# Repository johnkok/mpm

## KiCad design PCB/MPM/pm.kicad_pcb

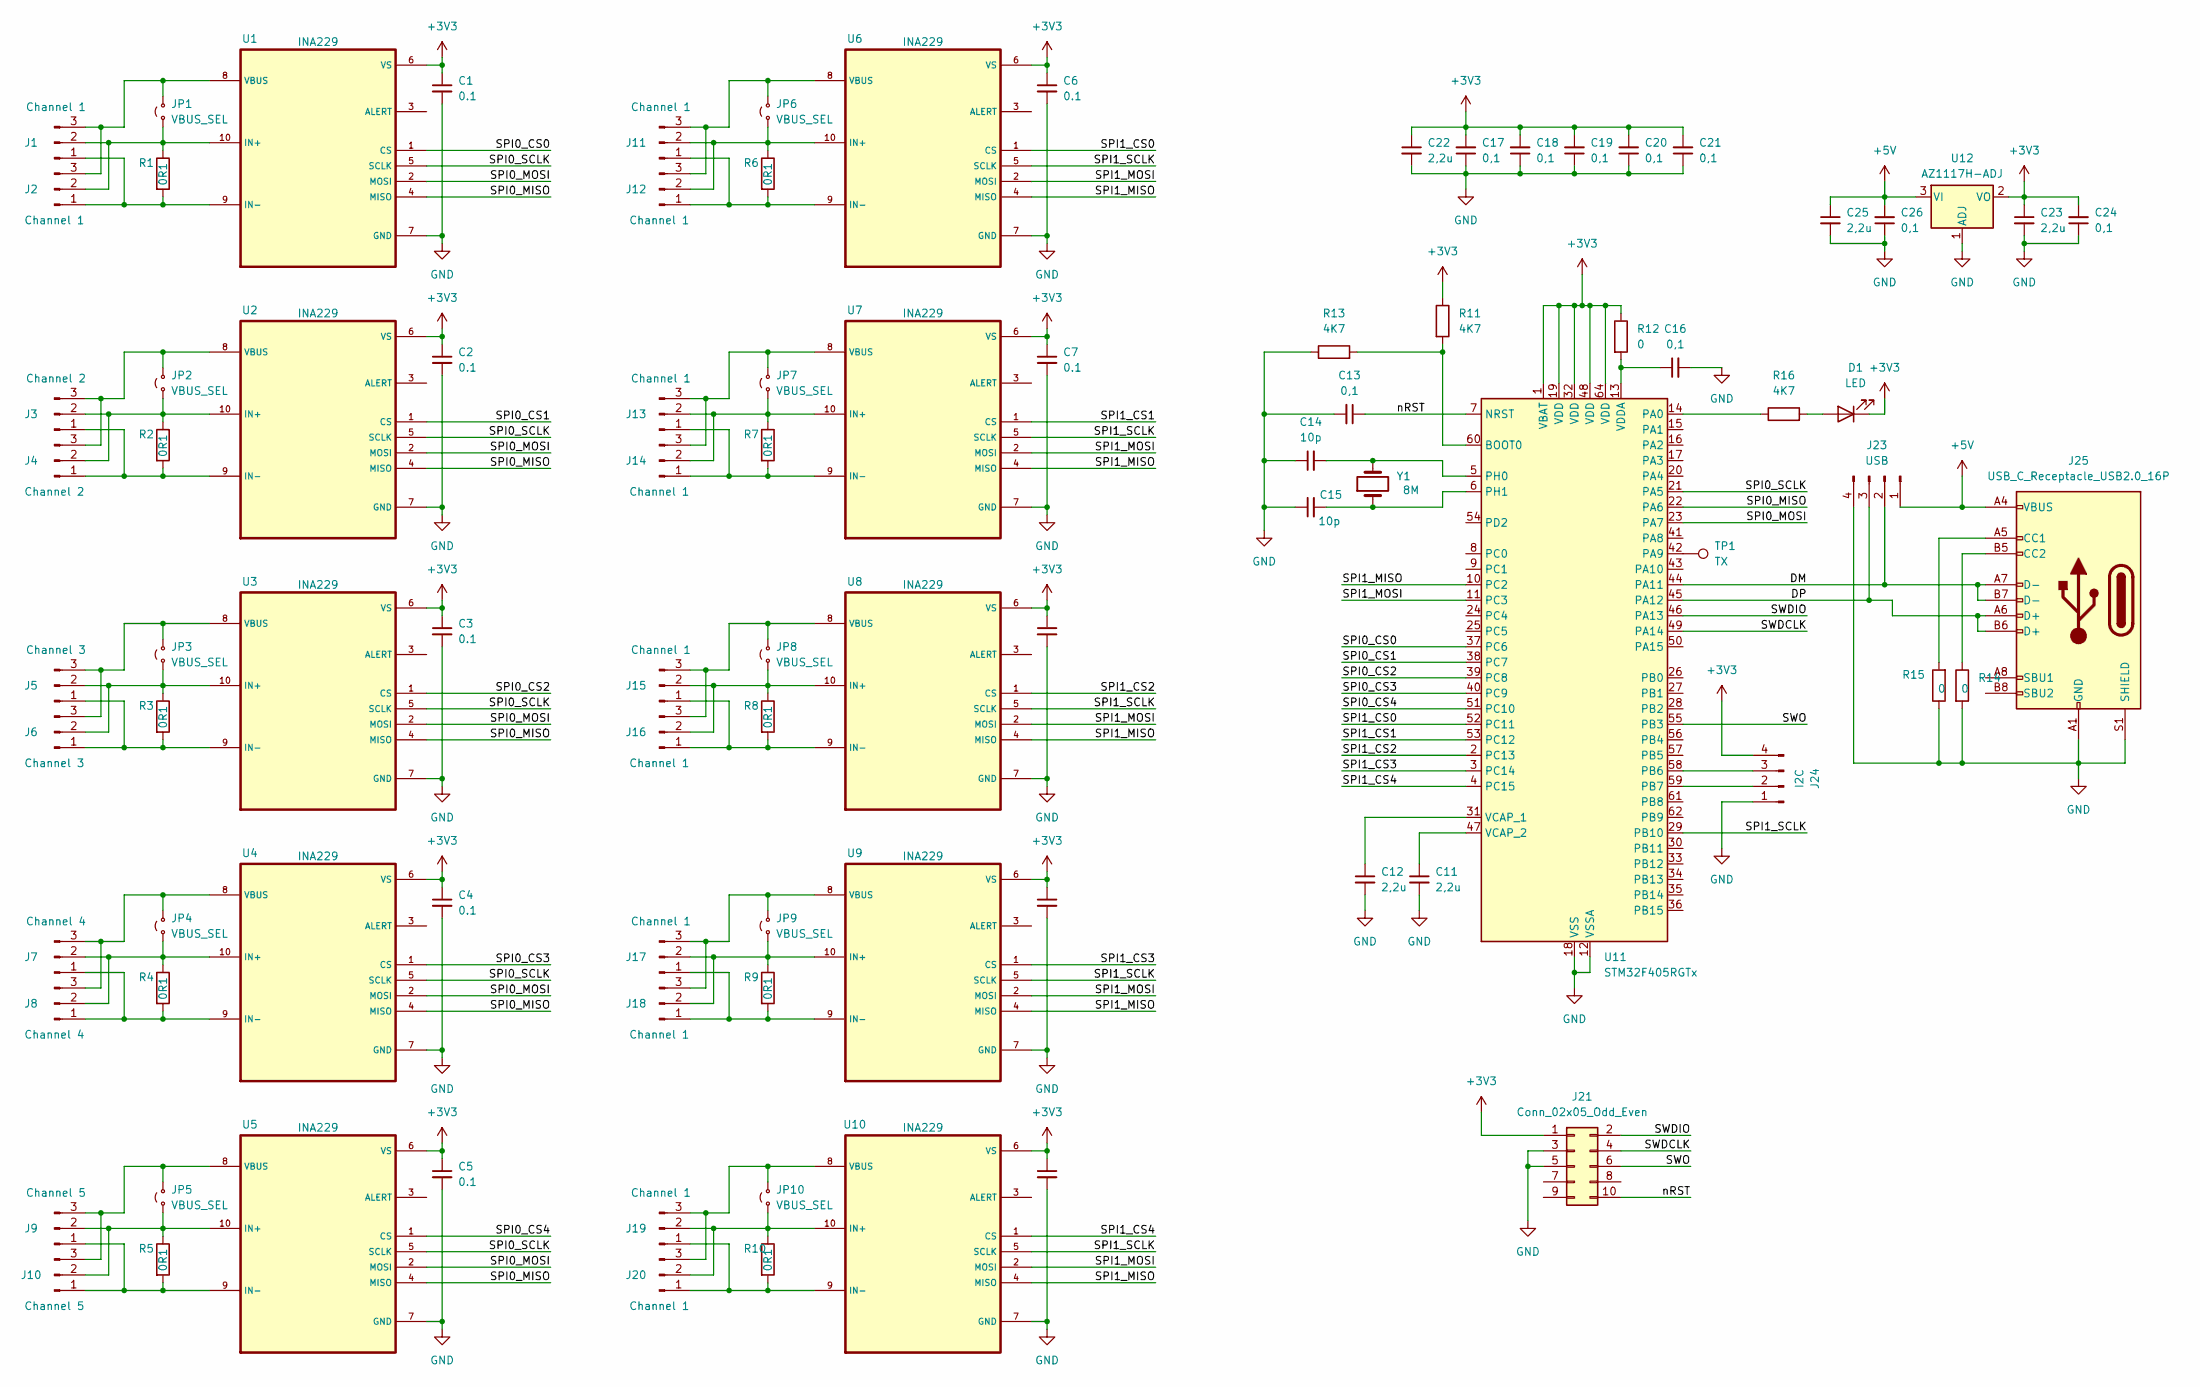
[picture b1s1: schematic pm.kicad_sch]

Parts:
C1, C2, C3, C4, C5, C6, C7, C8, C9, C10: 0.1; C_0603_1608Metric_Pad1.08x0.95mm_HandSolder
C11, C12, C22, C23, C25: 2,2u; C_0805_2012Metric_Pad1.18x1.45mm_HandSolder
C13, C16, C17, C18, C19, C20, C21, C24, C26: 0,1; C_0603_1608Metric_Pad1.08x0.95mm_HandSolder
C14, C15: 10p; C_0603_1608Metric_Pad1.08x0.95mm_HandSolder
D1: LED; LED_0603_1608Metric
J1, J11, J13, J15, J17, J19: Channel 1; PinHeader_1x03_P2.54mm_Vertical
J2, J12, J14, J16, J18, J20: Channel 1; PhoenixContact_MCV_1,5_3-G-5.08_1x03_P5.08mm_Vertical
J3: Channel 2; PinHeader_1x03_P2.54mm_Vertical
J4: Channel 2; PhoenixContact_MCV_1,5_3-G-5.08_1x03_P5.08mm_Vertical
J5: Channel 3; PinHeader_1x03_P2.54mm_Vertical
J6: Channel 3; PhoenixContact_MCV_1,5_3-G-5.08_1x03_P5.08mm_Vertical
J7: Channel 4; PinHeader_1x03_P2.54mm_Vertical
J8: Channel 4; PhoenixContact_MCV_1,5_3-G-5.08_1x03_P5.08mm_Vertical
J9: Channel 5; PinHeader_1x03_P2.54mm_Vertical
J10: Channel 5; PhoenixContact_MCV_1,5_3-G-5.08_1x03_P5.08mm_Vertical
J21: Conn_02x05_Odd_Even; PinHeader_2x05_P2.54mm_Vertical
J23: USB; PinHeader_1x04_P2.54mm_Vertical
J24: I2C; PinHeader_1x04_P2.54mm_Vertical
J25: USB_C_Receptacle_USB2.0_16P; USB_C_Receptacle_GCT_USB4105-xx-A_16P_TopMnt_Horizontal
JP1, JP2, JP3, JP4, JP5, JP6, JP7, JP8, JP9, JP10: VBUS_SEL; PinHeader_1x02_P2.54mm_Vertical
R1, R2, R3, R4, R5, R6, R7, R8, R9, R10: 0R1; R_1206_3216Metric_Pad1.30x1.75mm_HandSolder
R11, R13, R16: 4K7; R_0603_1608Metric_Pad0.98x0.95mm_HandSolder
R12, R14, R15: 0; R_0603_1608Metric_Pad0.98x0.95mm_HandSolder
TP1: TX; TestPoint_Loop_D1.80mm_Drill1.0mm_Beaded
U1, U2, U3, U4, U5, U6, U7, U8, U9, U10: INA229; VSSOP-10_3x3mm_P0.5mm
U11: STM32F405RGTx; LQFP-64_10x10mm_P0.5mm
U12: AZ1117H-ADJ; SOT-223-3_TabPin2
Y1: 8M; Crystal_HC18-U_Vertical

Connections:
+3V3: C1.1, C2.1, C3.1, C4.1, C5.1, C6.1, C7.1, C8.1, C9.1, C10.1, C17.2, C18.2, C19.2, C20.2, C21.2, C22.1, C23.1, C24.2, D1.1 (K), J21.1, J24.4, R11.1, R12.1, U1.6 (VS), U2.6 (VS), U3.6 (VS), U4.6 (VS), U5.6 (VS), U6.6 (VS), U7.6 (VS), U8.6 (VS), U9.6 (VS), U10.6 (VS), U11.1 (VBAT), U11.19 (VDD), U11.32 (VDD), U11.48 (VDD), U11.64 (VDD), U12.2 (VO)
+5V: C25.1, C26.2, J23.1, J25.A4 (VBUS), J25.A9 (VBUS), J25.B4 (VBUS), J25.B9 (VBUS), U12.3 (VI)
/DM: J23.2, J25.A7 (D-), J25.B7 (D-), U11.44 (PA11)
/DP: J23.3, J25.A6 (D+), J25.B6 (D+), U11.45 (PA12)
/SPI0_CS0: U1.1 (CS), U11.37 (PC6)
/SPI0_CS1: U2.1 (CS), U11.38 (PC7)
/SPI0_CS2: U3.1 (CS), U11.39 (PC8)
/SPI0_CS3: U4.1 (CS), U11.40 (PC9)
/SPI0_CS4: U5.1 (CS), U11.51 (PC10)
/SPI0_MISO: U1.4 (MISO), U2.4 (MISO), U3.4 (MISO), U4.4 (MISO), U5.4 (MISO), U11.22 (PA6)
/SPI0_MOSI: U1.2 (MOSI), U2.2 (MOSI), U3.2 (MOSI), U4.2 (MOSI), U5.2 (MOSI), U11.23 (PA7)
/SPI0_SCLK: U1.5 (SCLK), U2.5 (SCLK), U3.5 (SCLK), U4.5 (SCLK), U5.5 (SCLK), U11.21 (PA5)
/SPI1_CS0: U6.1 (CS), U11.52 (PC11)
/SPI1_CS1: U7.1 (CS), U11.53 (PC12)
/SPI1_CS2: U8.1 (CS), U11.2 (PC13)
/SPI1_CS3: U9.1 (CS), U11.3 (PC14)
/SPI1_CS4: U10.1 (CS), U11.4 (PC15)
/SPI1_MISO: U6.4 (MISO), U7.4 (MISO), U8.4 (MISO), U9.4 (MISO), U10.4 (MISO), U11.10 (PC2)
/SPI1_MOSI: U6.2 (MOSI), U7.2 (MOSI), U8.2 (MOSI), U9.2 (MOSI), U10.2 (MOSI), U11.11 (PC3)
/SPI1_SCLK: U6.5 (SCLK), U7.5 (SCLK), U8.5 (SCLK), U9.5 (SCLK), U10.5 (SCLK), U11.29 (PB10)
/SWDCLK: J21.4, U11.49 (PA14)
/SWDIO: J21.2, U11.46 (PA13)
/SWO: J21.6, U11.55 (PB3)
/nRST: C13.1, J21.10, U11.7 (NRST)
GND: C1.2, C2.2, C3.2, C4.2, C5.2, C6.2, C7.2, C8.2, C9.2, C10.2, C11.2, C12.2, C13.2, C14.1, C15.1, C16.2, C17.1, C18.1, C19.1, C20.1, C21.1, C22.2, C23.2, C24.1, C25.2, C26.1, J21.3, J21.5, J23.4, J24.1, J25.A1 (GND), J25.A12 (GND), J25.B1 (GND), J25.B12 (GND), J25.S1 (SHIELD), R13.1, R14.2, R15.1, U1.7 (GND), U2.7 (GND), U3.7 (GND), U4.7 (GND), U5.7 (GND), U6.7 (GND), U7.7 (GND), U8.7 (GND), U9.7 (GND), U10.7 (GND), U11.12 (VSSA), U11.18 (VSS), U11.63 (VSS), U12.1 (ADJ)
unnamed: D1.2 (A), R16.2
unnamed: J1.1, J2.1, R1.2, U1.9 (IN-)
unnamed: J1.2, J2.2, JP1.1 (A), R1.1, U1.10 (IN+)
unnamed: J1.3, J2.3, JP1.2 (B), U1.8 (VBUS)
unnamed: J3.1, J4.1, R2.2, U2.9 (IN-)
unnamed: J3.2, J4.2, JP2.1 (A), R2.1, U2.10 (IN+)
unnamed: J3.3, J4.3, JP2.2 (B), U2.8 (VBUS)
unnamed: J5.1, J6.1, R3.2, U3.9 (IN-)
unnamed: J5.2, J6.2, JP3.1 (A), R3.1, U3.10 (IN+)
unnamed: J5.3, J6.3, JP3.2 (B), U3.8 (VBUS)
unnamed: J7.1, J8.1, R4.2, U4.9 (IN-)
unnamed: J7.2, J8.2, JP4.1 (A), R4.1, U4.10 (IN+)
unnamed: J7.3, J8.3, JP4.2 (B), U4.8 (VBUS)
unnamed: J9.1, J10.1, R5.2, U5.9 (IN-)
unnamed: J9.2, J10.2, JP5.1 (A), R5.1, U5.10 (IN+)
unnamed: J9.3, J10.3, JP5.2 (B), U5.8 (VBUS)
unnamed: J11.1, J12.1, R6.2, U6.9 (IN-)
unnamed: J11.2, J12.2, JP6.1 (A), R6.1, U6.10 (IN+)
unnamed: J11.3, J12.3, JP6.2 (B), U6.8 (VBUS)
unnamed: J13.1, J14.1, R7.2, U7.9 (IN-)
unnamed: J13.2, J14.2, JP7.1 (A), R7.1, U7.10 (IN+)
unnamed: J13.3, J14.3, JP7.2 (B), U7.8 (VBUS)
unnamed: J15.1, J16.1, R8.2, U8.9 (IN-)
unnamed: J15.2, J16.2, JP8.1 (A), R8.1, U8.10 (IN+)
unnamed: J15.3, J16.3, JP8.2 (B), U8.8 (VBUS)
unnamed: J17.1, J18.1, R9.2, U9.9 (IN-)
unnamed: J17.2, J18.2, JP9.1 (A), R9.1, U9.10 (IN+)
unnamed: J17.3, J18.3, JP9.2 (B), U9.8 (VBUS)
unnamed: J19.1, J20.1, R10.2, U10.9 (IN-)
unnamed: J19.2, J20.2, JP10.1 (A), R10.1, U10.10 (IN+)
unnamed: J19.3, J20.3, JP10.2 (B), U10.8 (VBUS)
unnamed: J24.2, U11.59 (PB7)
unnamed: J24.3, U11.58 (PB6)
unnamed: J25.A5 (CC1), R15.2
unnamed: J25.B5 (CC2), R14.1
unnamed: R11.2, R13.2, U11.60 (BOOT0)
unnamed: R16.1, U11.14 (PA0)
unnamed: TP1.1, U11.42 (PA9)
unnamed: C14.2, U11.5 (PH0), Y1.2
unnamed: C15.2, U11.6 (PH1), Y1.1
unnamed: C12.1, U11.31 (VCAP_1)
unnamed: C11.1, U11.47 (VCAP_2)
unnamed: C16.1, R12.2, U11.13 (VDDA)

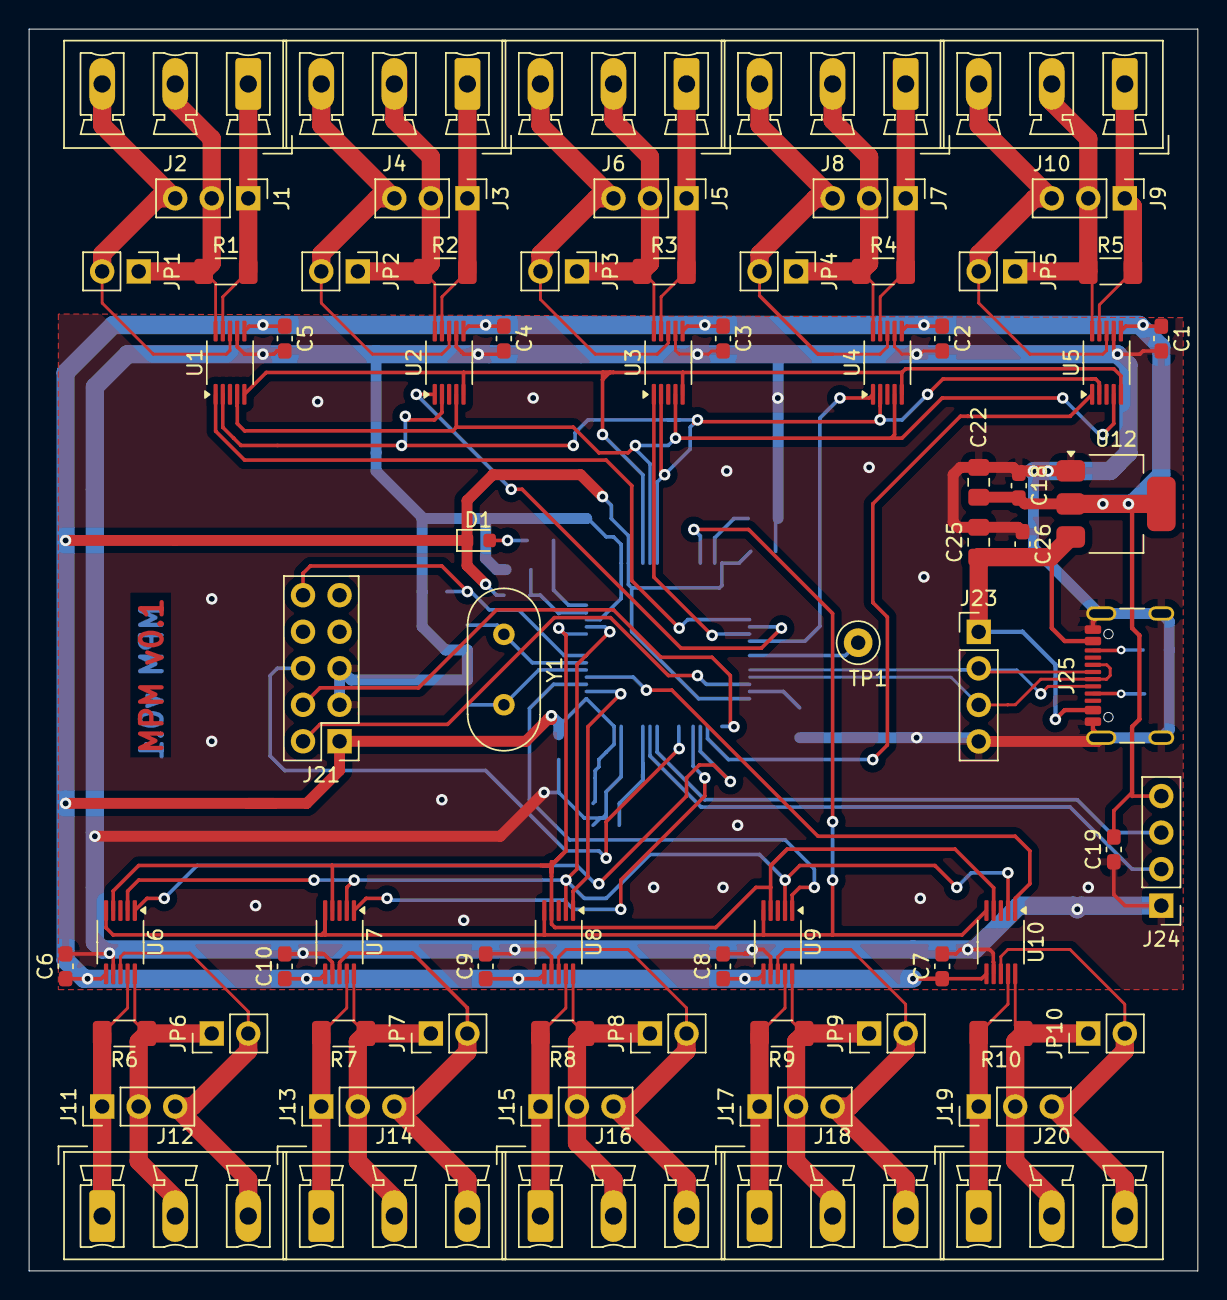
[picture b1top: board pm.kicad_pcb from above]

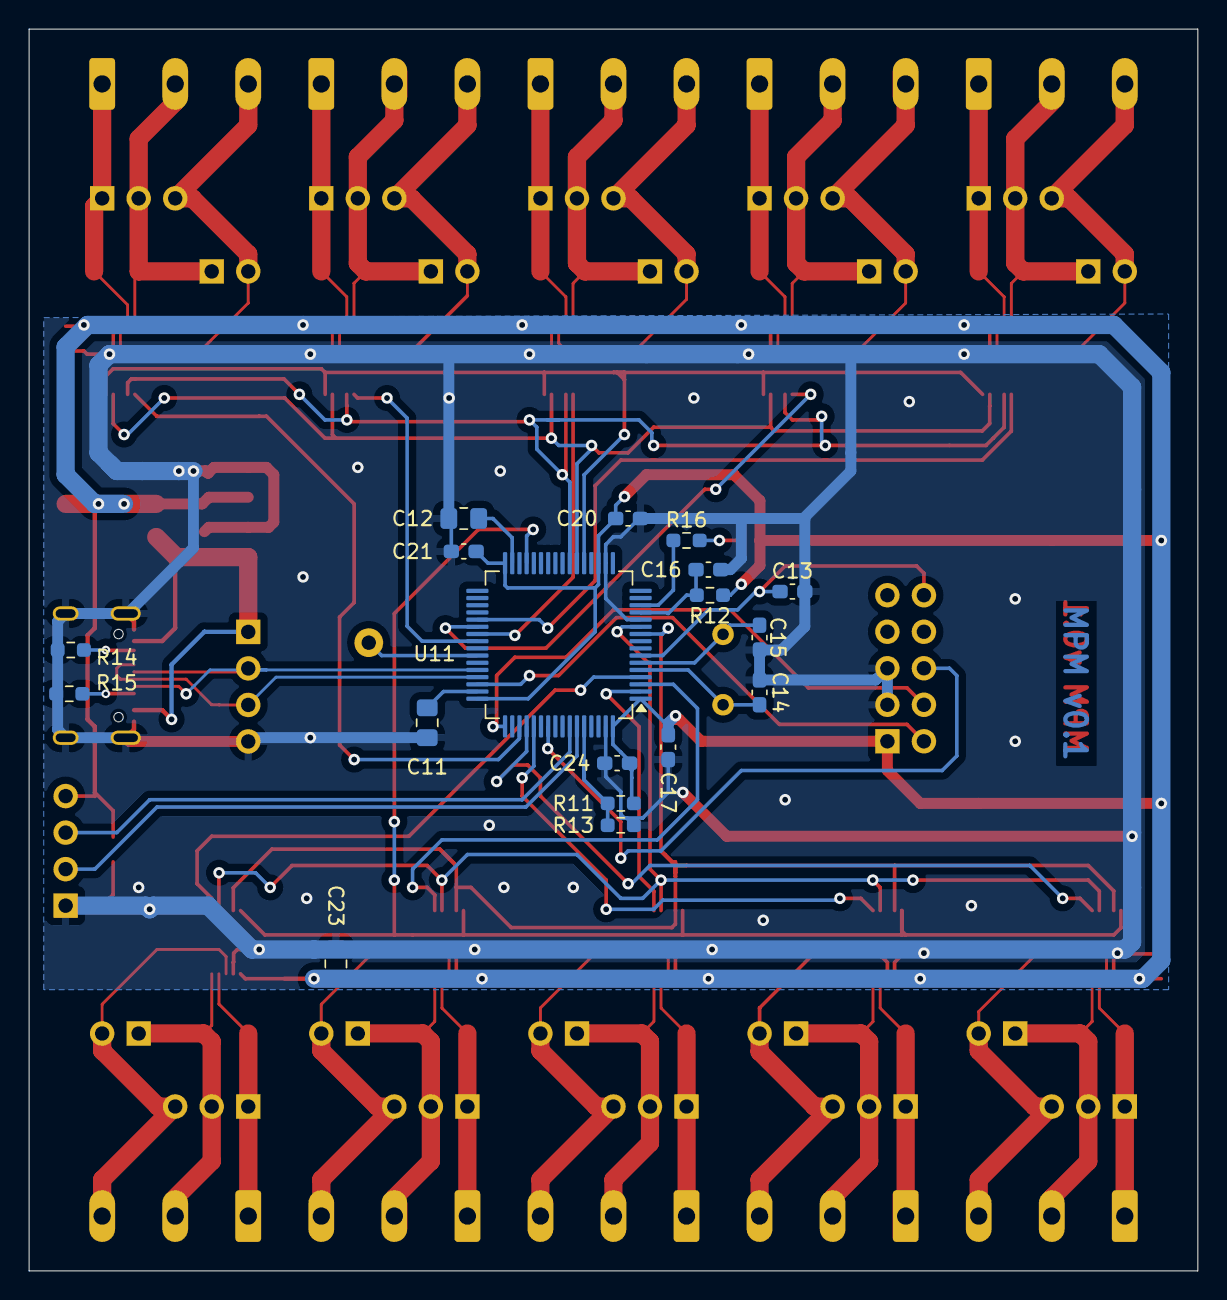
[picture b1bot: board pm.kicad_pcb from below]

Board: 2 copper layers, 81.3 x 86.4 mm, 91 parts (18 on the bottom side), 68 nets.

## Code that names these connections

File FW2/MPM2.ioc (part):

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Mcu.Name=STM32F405RGTx
Mcu.Package=LQFP64
Mcu.UserName=STM32F405RGTx
PA0-WKUP.GPIOParameters=PinState,GPIO_PuPd,GPIO_Label,GPIO_ModeDefaultOutputPP
PA0-WKUP.GPIO_Label=LED
PA0-WKUP.GPIO_ModeDefaultOutputPP=GPIO_MODE_OUTPUT_OD
PA0-WKUP.GPIO_PuPd=GPIO_NOPULL
PA0-WKUP.PinState=GPIO_PIN_SET
PA0-WKUP.Signal=GPIO_Output
PA10.Mode=Asynchronous
PA10.Signal=USART1_RX
PA11.Mode=Device_Only
PA11.Signal=USB_OTG_FS_DM
PA12.Mode=Device_Only
PA12.Signal=USB_OTG_FS_DP
PA13.Signal=SYS_JTMS-SWDIO
PA14.Signal=SYS_JTCK-SWCLK
PA5.Mode=Full_Duplex_Master
PA5.Signal=SPI1_SCK
PA6.Mode=Full_Duplex_Master
PA6.Signal=SPI1_MISO
PA7.Mode=Full_Duplex_Master
PA7.Signal=SPI1_MOSI
PA9.Mode=Asynchronous
PA9.Signal=USART1_TX
PB10.Mode=Full_Duplex_Master
PB10.Signal=SPI2_SCK
PB6.Mode=I2C
PB6.Signal=I2C1_SCL
PB7.Mode=I2C
PB7.Signal=I2C1_SDA
PC10.GPIOParameters=GPIO_Speed,PinState,GPIO_PuPd,GPIO_Label
PC10.GPIO_Label=nCS_A4
PC10.GPIO_PuPd=GPIO_PULLUP
PC10.GPIO_Speed=GPIO_SPEED_FREQ_HIGH
PC10.PinState=GPIO_PIN_SET
PC10.Signal=GPIO_Output
PC11.GPIOParameters=GPIO_Speed,PinState,GPIO_PuPd,GPIO_Label
PC11.GPIO_Label=nCS_B0
PC11.GPIO_PuPd=GPIO_PULLUP
PC11.GPIO_Speed=GPIO_SPEED_FREQ_HIGH
PC11.PinState=GPIO_PIN_SET
PC11.Signal=GPIO_Output
PC12.GPIOParameters=GPIO_Speed,PinState,GPIO_PuPd,GPIO_Label
PC12.GPIO_Label=nCS_B1
PC12.GPIO_PuPd=GPIO_PULLUP
PC12.GPIO_Speed=GPIO_SPEED_FREQ_HIGH
PC12.PinState=GPIO_PIN_SET
PC12.Signal=GPIO_Output
PC13-ANTI_TAMP.GPIOParameters=PinState,GPIO_PuPd,GPIO_Label
PC13-ANTI_TAMP.GPIO_Label=nCS_B2
PC13-ANTI_TAMP.GPIO_PuPd=GPIO_PULLUP
PC13-ANTI_TAMP.PinState=GPIO_PIN_SET
PC13-ANTI_TAMP.Signal=GPIO_Output
PC14-OSC32_IN.GPIOParameters=PinState,GPIO_PuPd,GPIO_Label
PC14-OSC32_IN.GPIO_Label=nCS_B3
PC14-OSC32_IN.GPIO_PuPd=GPIO_PULLUP
PC14-OSC32_IN.PinState=GPIO_PIN_SET
PC14-OSC32_IN.Signal=GPIO_Output
PC15-OSC32_OUT.GPIOParameters=PinState,GPIO_PuPd,GPIO_Label
PC15-OSC32_OUT.GPIO_Label=nCS_B4
PC15-OSC32_OUT.GPIO_PuPd=GPIO_PULLUP
PC15-OSC32_OUT.PinState=GPIO_PIN_SET
PC15-OSC32_OUT.Signal=GPIO_Output
PC2.Mode=Full_Duplex_Master
PC2.Signal=SPI2_MISO
PC3.Mode=Full_Duplex_Master
PC3.Signal=SPI2_MOSI
PC6.GPIOParameters=GPIO_Speed,PinState,GPIO_PuPd,GPIO_Label
PC6.GPIO_Label=nCS_A0
PC6.GPIO_PuPd=GPIO_PULLUP
PC6.GPIO_Speed=GPIO_SPEED_FREQ_HIGH
PC6.PinState=GPIO_PIN_SET
PC6.Signal=GPIO_Output
PC7.GPIOParameters=GPIO_Speed,PinState,GPIO_PuPd,GPIO_Label
PC7.GPIO_Label=nCS_A1
PC7.GPIO_PuPd=GPIO_PULLUP
PC7.GPIO_Speed=GPIO_SPEED_FREQ_HIGH
PC7.PinState=GPIO_PIN_SET
PC7.Signal=GPIO_Output
PC8.GPIOParameters=GPIO_Speed,PinState,GPIO_PuPd,GPIO_Label
PC8.GPIO_Label=nCS_A2
PC8.GPIO_PuPd=GPIO_PULLUP
PC8.GPIO_Speed=GPIO_SPEED_FREQ_HIGH
PC8.PinState=GPIO_PIN_SET
PC8.Signal=GPIO_Output
PC9.GPIOParameters=GPIO_Speed,PinState,GPIO_PuPd,GPIO_Label
PC9.GPIO_Label=nCS_A3
PC9.GPIO_PuPd=GPIO_PULLUP
PC9.GPIO_Speed=GPIO_SPEED_FREQ_HIGH
PC9.PinState=GPIO_PIN_SET
PC9.Signal=GPIO_Output
PH0-OSC_IN.Mode=HSE-External-Oscillator
PH0-OSC_IN.Signal=RCC_OSC_IN
PH1-OSC_OUT.Mode=HSE-External-Oscillator
PH1-OSC_OUT.Signal=RCC_OSC_OUT
RCC.HSE_VALUE=8000000
RCC.SYSCLKFreq_VALUE=168000000
RCC.SYSCLKSource=RCC_SYSCLKSOURCE_PLLCLK
board=custom
